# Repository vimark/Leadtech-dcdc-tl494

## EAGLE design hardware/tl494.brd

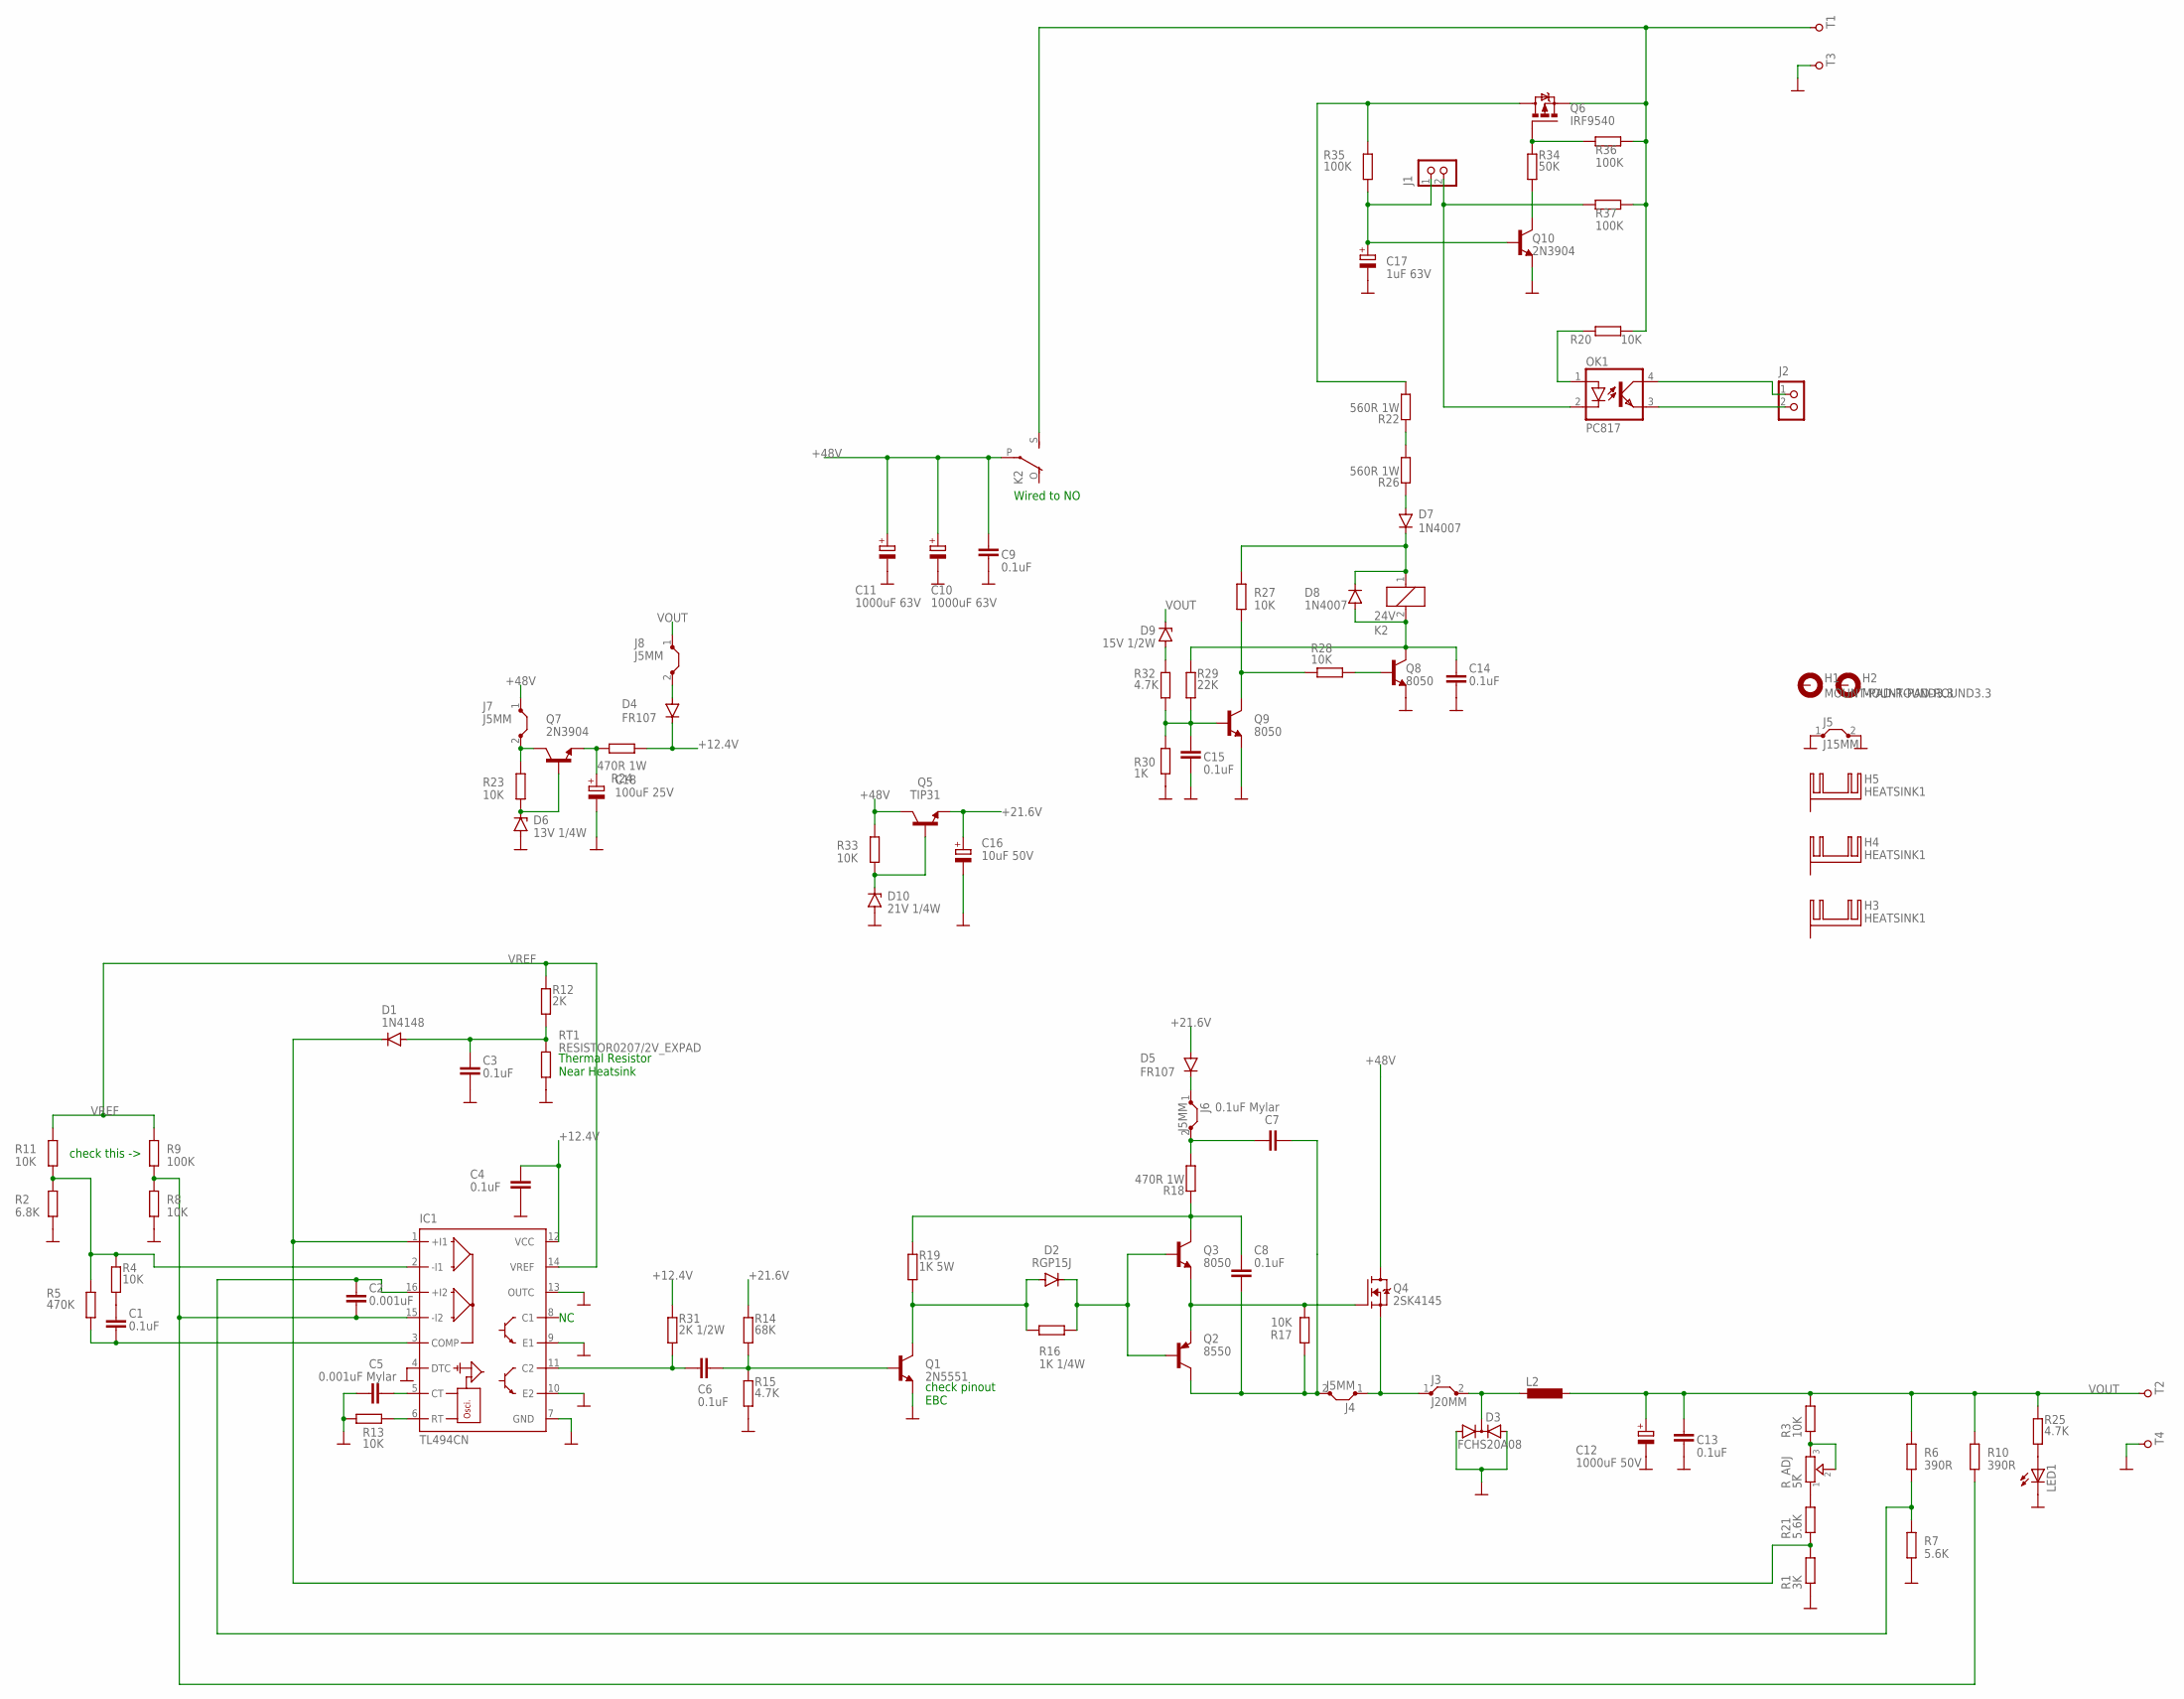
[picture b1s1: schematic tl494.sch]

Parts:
C1, C3, C4, C6, C8, C9, C13, C14, C15: 0.1uF; C050-024X044_EXPAD
C2: 0.001uF; C050-024X044_EXPAD
C5: 0.001uF Mylar; C050-024X044_EXPAD
C7: 0.1uF Mylar; C050-050X075_EXPAD
C10, C11: 1000uF 63V; E7,5-18
C12: 1000uF 50V; E5-13
C16: 10uF 50V; E2,5-7_EXPAD
C17: 1uF 63V; E2-5_EXPAD
C18: 100uF 25V; E2,5-7_EXPAD
D1: 1N4148; DO35-10
D2: RGP15J; DO41-10
D3: FCHS20A08; TO220ABS
D4, D5: FR107; DO41-10
D6: 13V 1/4W; DO34Z7
D7, D8: 1N4007; DO41-10
D9: 15V 1/2W; DO34Z7
D10: 21V 1/4W; DO34Z7
H1, H2: MOUNT-PAD-ROUND3.3; 3,3-PAD
H3, H4, H5: HEATSINK1; TO-220_HEATSINK1
IC1: TL494CN; DIL16
J1, J2: CON_HEADER_1X02-PTH; M1X2
J3: J20MM; 20
J4, J6, J7, J8: J5MM; 05
J5: J15MM; 15
K2: 24V; G5LE
L2: L-EUTJ5-U1; TJ5-U1
LED1: LED-5MM
OK1: PC817; DIL04
Q1: 2N5551; TO-92
Q2: 8550; TO-92
Q3, Q8, Q9: 8050; TO-92
Q4: 2SK4145; TO-220V
Q5: TIP31; TO-220V
Q6: IRF9540; TO220BV
Q7, Q10: 2N3904; TO-92
R1: 3K; 0207/10_EXPAD
R2: 6.8K; 0207/10_EXPAD
R3, R11, R20, R27, R28: 10K; 0207/10_EXPAD
R4, R8, R13, R17, R23, R33: 10K; 0207/2V_EXPAD
R5: 470K; 0207/2V_EXPAD
R6, R10: 390R; 0207/10_EXPAD
R7, R21: 5.6K; 0207/2V_EXPAD
R9: 100K; 0207/10_EXPAD
R12: 2K; 0207/10_EXPAD
R14: 68K; 0207/2V_EXPAD
R15, R32: 4.7K; 0207/2V_EXPAD
R16: 1K 1/4W; 0207/10_EXPAD
R18, R24: 470R 1W; 0414V_EXPAD
R19: 1K 5W; 0414V_EXPAD
R22, R26: 560R 1W; 0414V_EXPAD
R25: 4.7K; 0207/10_EXPAD
R29: 22K; 0207/10_EXPAD
R30: 1K; 0207/2V_EXPAD
R31: 2K 1/2W; 0207/2V_EXPAD
R34: 50K; 0207/2V_EXPAD
R35: 100K; 0207/2V_EXPAD
R36: 100K; 0207/2V
R37: 100K; 0207/10
RT1: RESISTOR0207/2V_EXPAD; 0207/2V_EXPAD
R_ADJ: 5K; TRIMMER_3362P_EXPAD
T1, T2, T4: PAD_TERMINAL-1.02MM_ROUND; CON_PAD_ROUND_1.02MM
T3: PAD_TERMINAL-1.02MM_SQUARE; CON_PAD_SQUARE_1.02MM

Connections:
+12.4V: C4.2, D4.C, IC1.12 (VCC), R24.1, R31.2
+21.6V: C16.+, D5.A, Q5.3 (E), R14.2
+48V: C9.1, C10.+, C11.+, J7.1, K2.P, Q4.2 (D), Q5.2 (C), R33.1
GND: C3.1, C4.1, C5.2, C9.2, C10.-, C11.-, C12.-, C13.2, C14.2, C15.2, C16.-, C17.-, C18.-, D3.A1, D3.A2, D6.A, D10.A, IC1.4 (DTC), IC1.7 (GND), IC1.9 (E1), IC1.10 (E2), IC1.13 (OUTC), J5.1, J5.2, LED1.K (C), Q1.1 (E), Q8.1 (E), Q9.1 (E), Q10.1 (E), R1.1, R2.1, R7.1, R8.1, R13.1, R15.1, R30.1, RT1.2, T3.P, T4.P
unnamed: C2.2, IC1.16 (+I2), R6.1, R7.2
unnamed: R3.1, R_ADJ.2, R_ADJ.3
unnamed: R21.2, R_ADJ.1
unnamed: IC1.2 (-I1), R2.2, R4.2, R5.1, R11.1
unnamed: C1.2, R4.1
unnamed: C1.1, IC1.3 (COMP), R5.2
unnamed: D1.C, IC1.1 (+I1), R1.2, R21.1
unnamed: C2.1, IC1.15 (-I2), R8.2, R9.2, R10.2
unnamed: C3.2, D1.A, R12.1, RT1.1
unnamed: C6.2, IC1.11 (C2), R31.1
unnamed: C5.1, IC1.5 (CT)
unnamed: IC1.6 (RT), R13.2
unnamed: C6.1, Q1.2 (B), R14.1, R15.2
unnamed: D2.A, Q1.3 (C), R16.1, R19.1
unnamed: D2.C, Q2.2 (B), Q3.2 (B), R16.2
unnamed: Q2.1 (E), Q3.1 (E), Q4.1 (G), R17.2
unnamed: C7.2, C8.2, J4.2, Q2.3 (C), R17.1
unnamed: C8.1, Q3.3 (C), R18.2, R19.2
unnamed: C7.1, J6.2, R18.1
unnamed: OK1.1 (A), R20.2
unnamed: LED1.A, R25.1
unnamed: D7.A, R26.2
unnamed: D7.C, D8.C, K2.1, R27.2
unnamed: C14.1, D8.A, K2.2, Q8.3 (C), R29.2
unnamed: Q9.3 (C), R27.1, R28.1
unnamed: Q8.2 (B), R28.2
unnamed: C15.1, Q9.2 (B), R29.1, R30.2, R32.2
unnamed: D9.A, R32.1
unnamed: J2.1, OK1.4 (COL)
unnamed: Q6.G, R34.2, R36.2
unnamed: Q10.3 (C), R34.1
unnamed: Q6.D, R22.1, R35.2
unnamed: C17.+, J1.1, Q10.2 (B), R35.1
unnamed: J1.2, OK1.2 (C), R37.2
unnamed: J2.2, OK1.3 (EMIT)
unnamed: R22.2, R26.1
unnamed: D3.C, J3.2, L2.2
unnamed: J3.1, J4.1, Q4.3 (S)
unnamed: D10.C, Q5.1 (B), R33.2
unnamed: D6.C, Q7.2 (B), R23.2
unnamed: C18.+, Q7.1 (E), R24.2
unnamed: D5.C, J6.1
unnamed: J7.2, Q7.3 (C), R23.1
unnamed: D4.A, J8.2
VIN: K2.S, Q6.S, R20.1, R36.1, R37.1, T1.P
VOUT: C12.+, C13.1, D9.C, J8.1, L2.1, R3.2, R6.2, R10.1, R25.2, T2.P
VREF: IC1.14 (VREF), R9.1, R11.2, R12.2

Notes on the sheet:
check this ->
Thermal Resistor Near Heatsink
Wired to NO
check pinout EBC

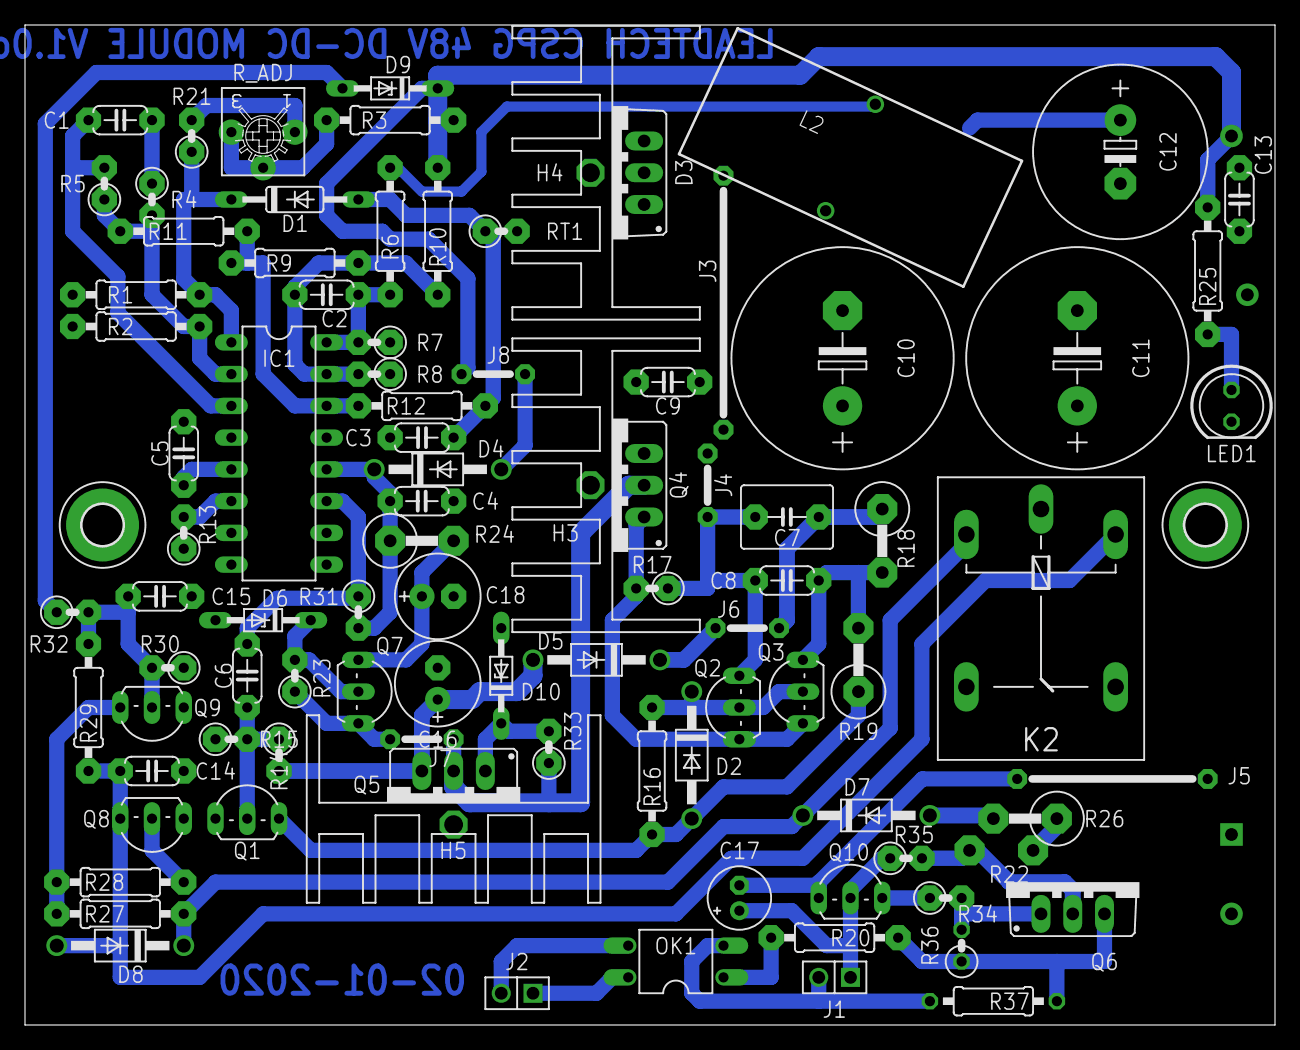
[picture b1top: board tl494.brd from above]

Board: 2 copper layers, 100.0 x 80.0 mm, 99 parts (1 on the bottom side), 51 nets.

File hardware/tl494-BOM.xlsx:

Qty | Value | Device | Package | Parts | Description
1 | FCH30A06 | DIODE-2AC|CATO220V | TO220ABS | D3 | Dual DIODE Anode-Cathode|Cathode-Anode
1 | RED LED | LED-5MM | LED-5MM | LED1 | Light Emitting Diode
1 | 330R | R-EU_0207/2V | 0207/2V | RT1 | RESISTOR, European symbol
1 | 0.001uF | C-EU050-024X044 | C050-024X044 | C2 | CAPACITOR, European symbol
1 | 0.001uF Mylar | C-EU050-024X044 | C050-024X044 | C5 | CAPACITOR, European symbol
9 | 0.1uF Ceramic | C-EU050-024X044 | C050-024X044 | C1, C3, C4, C6, C8, C9, C13, C14, C15 | CAPACITOR, European symbol
1 | 0.1uF Mylar | C-EU050-050X075 | C050-050X075 | C7 | CAPACITOR, European symbol
1 | 1000uF 50V | CPOL-EUE3.5-10 | E3,5-10 | C12 | POLARIZED CAPACITOR, European symbol
2 | 1000uF 63V |  |  | C10, C11
4 | 100K | R-EU_0207/10 | 0207/10 | R9, R35, R36, R37 | RESISTOR, European symbol
1 | 100uF 25V Electrolytic | CPOL-EUE2.5-7 | E2,5-7 | C16 | POLARIZED CAPACITOR, European symbol
8 | 10K | R-EU_0207/10 | 0207/10 | R3, R4, R8, R11, R17, R27, R28, R29 | RESISTOR, European symbol
1 | 10K | R-EU_0207/2V | 0207/2V | R13 | RESISTOR, European symbol
2 | 15V 1/2W | BZV10 | DO34Z7 | D9, D10 | Z DIODE
3 | 1K | R-EU_0207/10 | 0207/10 | R20, R22, R30 | RESISTOR, European symbol
1 | 1K 1/4W | R-EU_0207/10 | 0207/10 | R16 | RESISTOR, European symbol
2 | 1N4007 | 1N4933 | DO41-10 | D7, D8 | DIODE
2 | 1N4148 | 1N4148DO35-10 | DO35-10 | D1, D4 | DIODE
1 | 1uF 63V Electrolytic | CPOL-EUE3.5-10 | E3,5-10 | C17 | POLARIZED CAPACITOR, European symbol
1 | 24V relay | G2R | G2R | K1 | RELAY
1 | 2K | R-EU_0207/10 | 0207/10 | R12 | RESISTOR, European symbol
1 | 2K 1/2W | R-EU_0207/10 | 0207/10 | R31 | RESISTOR, European symbol
1 | 2K 1W | R-EU_0207/10 | 0207/10 | R18 | RESISTOR, European symbol
1 | 2N3904 | TRANSISTOR_BJT_NPN-TO-92-EBC | TO-92 | Q1I1 | Most commonly used is SOT23-BEC
1 | 2N5551 | TRANSISTOR_BJT_NPN-TO-92-EBC | TO-92 | Q1 | Most commonly used is SOT23-BEC
1 | 2SK4145 MOSFET | TRANSISTOR_MOSFET-N-TO220V | TO-220V | Q4
2 | 390R | R-EU_0207/10 | 0207/10 | R6, R10 | RESISTOR, European symbol
1 | 3K | R-EU_0207/10 | 0207/10 | R1 | RESISTOR, European symbol
3 | 4.7K | R-EU_0207/10 | 0207/10 | R15, R25, R32 | RESISTOR, European symbol
1 | 470K | R-EU_0207/10 | 0207/10 | R5 | RESISTOR, European symbol
1 | 4K 1/2W | R-EU_0207/10 | 0207/10 | R19 | RESISTOR, European symbol
1 | 4K 2W | R-EU_0414/5V | 0414V | R33 | RESISTOR, European symbol
2 | 5.6K | R-EU_0207/10 | 0207/10 | R7, R21 | RESISTOR, European symbol
1 | 50K | R-EU_0207/10 | 0207/10 | R34 | RESISTOR, European symbol
1 | 560*x2 1W (2 x 560 ohms) | R-EU_0207/10 | 0207/10 | R26 | RESISTOR, European symbol
1 | 5K | TRIMMER-3362P | TRIMMER_3362P | R_ADJ | Trimmer resistor
1 | 6.8K | R-EU_0207/10 | 0207/10 | R2 | RESISTOR, European symbol
1 | 68K | R-EU_0207/10 | 0207/10 | R14 | RESISTOR, European symbol
3 | S8050 Transistor | TRANSISTOR_BJT_NPN-TO-92-EBC | TO-92 | Q1I, Q2I, Q3 | Most commonly used is SOT23-BEC
1 | S8550 Transistor | TRANSISTOR_BJT_PNP-TO-92-EBC | TO-92 | Q2 | Most commonly used is SOT23-BEC
2 | FR107 Diode | 1N4933 | DO41-10 | D2, D5 | DIODE
1 | INDUCTOR-L1812 | INDUCTOR-L1812 | L1812 | L1 | Inductor
1 | IRF9540 MOSFET | IRF9530 | TO220BV | Q6 | P-CHANNEL HEXFET POWER-MOS-FET
1 | PC817 Opto | PC817 | DIL04 | OK1 | SHARP OPTO COUPLER
1 | SW_MEMBRANE | SW_MEMBRANE | SW_MEMBRANE | SW1
1 | TL494CN IC | TL494CN | DIL16 | IC1 | SWITCHMODE Pulse Width Modulation Control Circuit

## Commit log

2019-12-14 added schematic and reference document pictures
2019-12-14 changes on schematic and added spice model
2019-12-19 very tiny change in schematic
2019-12-28 added board
2020-01-01 minor update
2020-01-02 added turn on latch circuit and gitignore
2020-01-06 partial board placement and started fix on latch swith problem
2020-01-07 minor updates on board
2020-01-07 fix spice latch circuit, started routing
2020-01-08 done board routing
2020-01-09 fix text on board
2020-01-10 place values
2020-01-10 updated the board
2020-01-11 added measured values on schematic
2020-01-13 added micro-cap spice sim
2020-01-14 schematic tiny updates
2020-01-14 add inductor sim
2020-01-15 testing
2020-01-22 new bootstrap circuit doc
2020-02-05 add protection spice and tech doc on smps from mean-well
